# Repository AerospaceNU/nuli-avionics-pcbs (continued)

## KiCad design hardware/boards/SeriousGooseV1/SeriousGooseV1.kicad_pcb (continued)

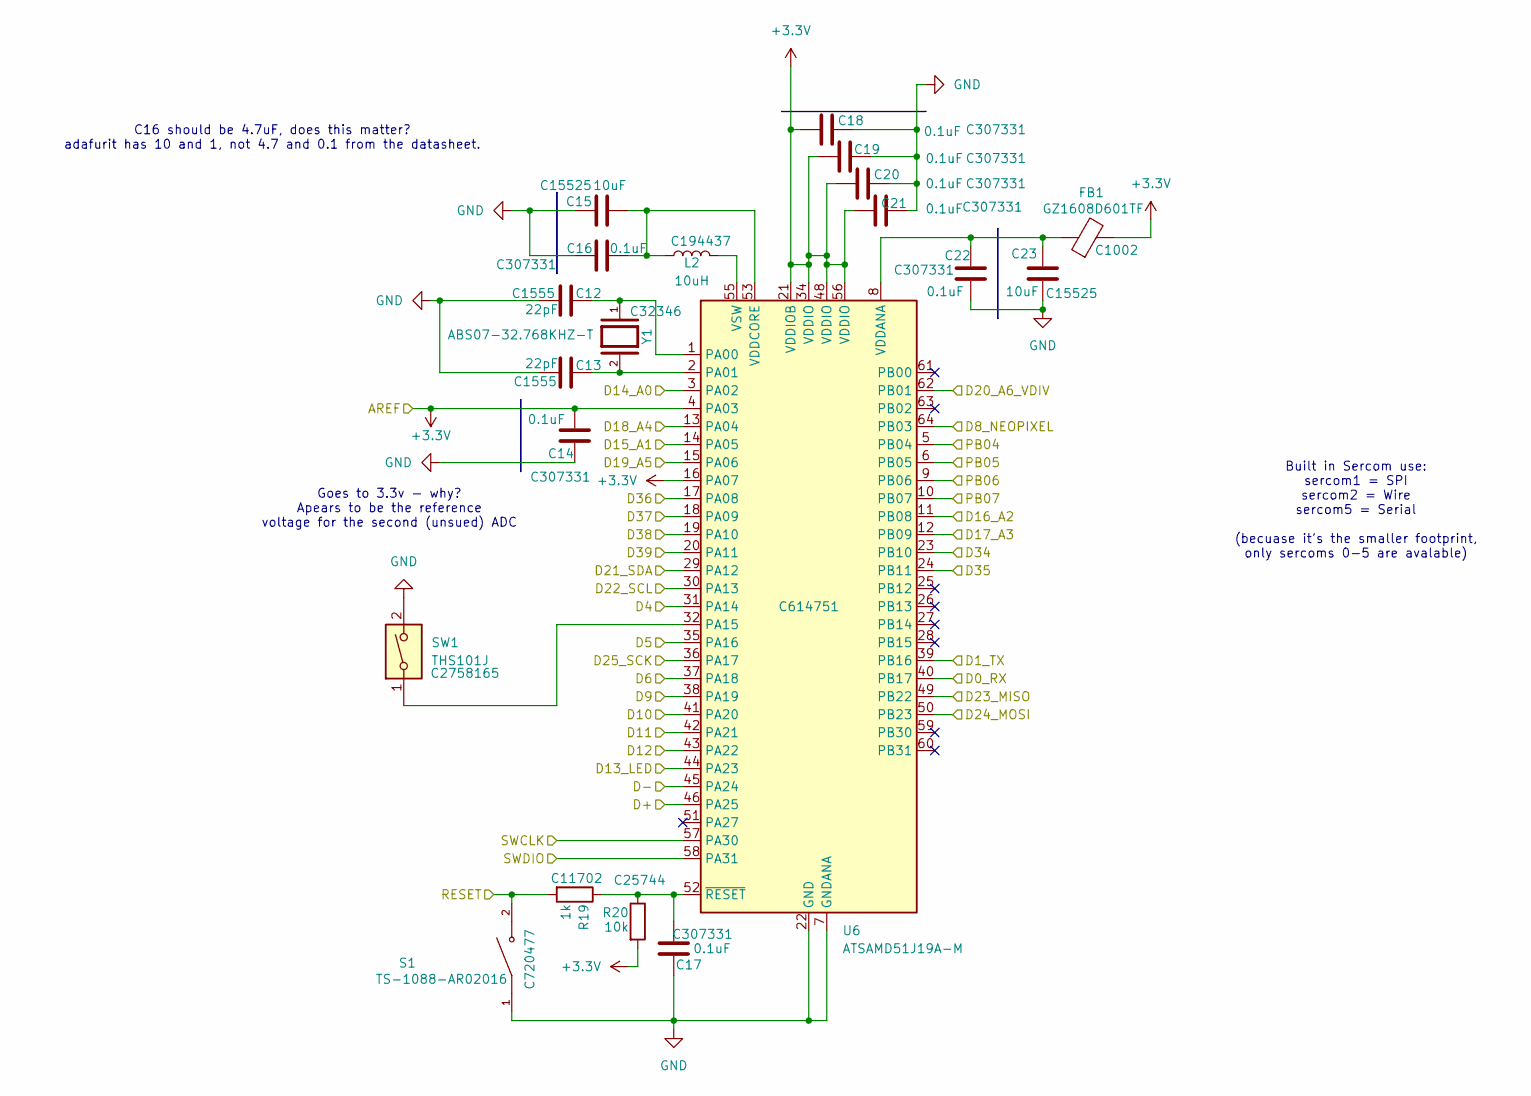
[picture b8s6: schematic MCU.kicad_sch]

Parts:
C12, C13: 22pF; C_0402_1005Metric; LCSC C1555
C14, C16, C17, C18, C19, C20, C21, C22: 0.1uF; C_0402_1005Metric; LCSC C307331
C15, C23: 10uF; C_0402_1005Metric; LCSC C15525
FB1: GZ1608D601TF; L_0603_1608Metric; LCSC C1002
L2: 10uH; L_0603_1608Metric; LCSC C194437
R19: 1k; R_0402_1005Metric; LCSC C11702
R20: 10k; R_0402_1005Metric; LCSC C25744
S1: TS-1088-AR02016; SW_TS-1088-AR02016; PARTREV N/A; LCSC C720477
SW1: THS101J; CHS-01TA; LCSC C2758165
U6: ATSAMD51J19A-M; QFN-64-1EP_9x9mm_P0.5mm_EP4.7x4.7mm; LCSC C614751
Y1: ABS07-32.768KHZ-T; XTAL_ABS07-32.768KHZ-T; PARTREV 08.19.15; LCSC C32346

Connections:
+3.3V: C14.2, C18.1, C19.1, C20.1, C21.1, FB1.2, R20.2, U6.4 (PA03), U6.16 (PA07), U6.21 (VDDIOB), U6.34 (VDDIO), U6.48 (VDDIO), U6.56 (VDDIO); also elsewhere on the board
/Connectors/AUX_1: U6.14 (PA05); also elsewhere on the board
/Connectors/AUX_2: U6.13 (PA04); also elsewhere on the board
/Connectors/AUX_3: U6.3 (PA02); also elsewhere on the board
/Connectors/D+: U6.46 (PA25); also elsewhere on the board
/Connectors/D-: U6.45 (PA24); also elsewhere on the board
/Connectors/RESET: R19.2, S1.2; also elsewhere on the board
/Connectors/SWCLK: U6.57 (PA30); also elsewhere on the board
/Connectors/SWDIO: U6.58 (PA31); also elsewhere on the board
/MCU/D0_RX: U6.40 (PB17); also elsewhere on the board
/MCU/D1_TX: U6.39 (PB16); also elsewhere on the board
/MCU/D4: U6.31 (PA14); also elsewhere on the board
/MCU/D5: U6.35 (PA16); also elsewhere on the board
/MCU/D6: U6.37 (PA18); also elsewhere on the board
/MCU/D8_NEOPIXEL: U6.64 (PB03)
/MCU/D9: U6.38 (PA19); also elsewhere on the board
/MCU/D10: U6.41 (PA20); also elsewhere on the board
/MCU/D11: U6.42 (PA21); also elsewhere on the board
/MCU/D12: U6.43 (PA22); also elsewhere on the board
/MCU/D13_LED: U6.44 (PA23)
/MCU/D16_A2: U6.11 (PB08); also elsewhere on the board
/MCU/D17_A3: U6.12 (PB09); also elsewhere on the board
/MCU/D19_A5: U6.15 (PA06); also elsewhere on the board
/MCU/D20_A6_VDIV: U6.62 (PB01); also elsewhere on the board
/MCU/D21_SDA: U6.29 (PA12); also elsewhere on the board
/MCU/D22_SCL: U6.30 (PA13); also elsewhere on the board
/MCU/D23_MISO: U6.49 (PB22); also elsewhere on the board
/MCU/D24_MOSI: U6.50 (PB23); also elsewhere on the board
/MCU/D25_SCK: U6.36 (PA17); also elsewhere on the board
/MCU/D34: U6.23 (PB10); also elsewhere on the board
/MCU/D35: U6.24 (PB11); also elsewhere on the board
/MCU/D36: U6.17 (PA08); also elsewhere on the board
/MCU/D37: U6.18 (PA09); also elsewhere on the board
/MCU/D38: U6.19 (PA10); also elsewhere on the board
/MCU/D39: U6.20 (PA11); also elsewhere on the board
/MCU/PB04: U6.5 (PB04); also elsewhere on the board
/MCU/PB05: U6.6 (PB05); also elsewhere on the board
/MCU/PB06: U6.9 (PB06); also elsewhere on the board
/MCU/PB07: U6.10 (PB07); also elsewhere on the board
GND: C12.2, C13.2, C14.1, C15.1, C16.2, C17.1, C18.2, C19.2, C20.2, C21.2, C22.2, C23.2, S1.1, SW1.2, U6.7 (GNDANA), U6.22 (GND), U6.33 (GND), U6.47 (GND), U6.54 (GND), U6.65 (GND); also elsewhere on the board
unnamed: C12.1, U6.1 (PA00), Y1.1
unnamed: C13.1, U6.2 (PA01), Y1.2
unnamed: SW1.1, U6.32 (PA15)
unnamed: C22.1, C23.1, FB1.1, U6.8 (VDDANA)
unnamed: C15.2, C16.1, L2.1, U6.53 (VDDCORE)
unnamed: L2.2, U6.55 (VSW)
unnamed: C17.2, R19.1, R20.1, U6.52 (~RESET)

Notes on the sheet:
Goes to 3.3v - why? Apears to be the reference voltage for the second (unsued) ADC
C16 should be 4.7uF, does this matter? adafurit has 10 and 1, not 4.7 and 0.1 from the datasheet.
Built in Sercom use: sercom1 = SPI sercom2 = Wire sercom5 = Serial (becuase it's the smaller footprint, only sercoms 0-5 are avalable)

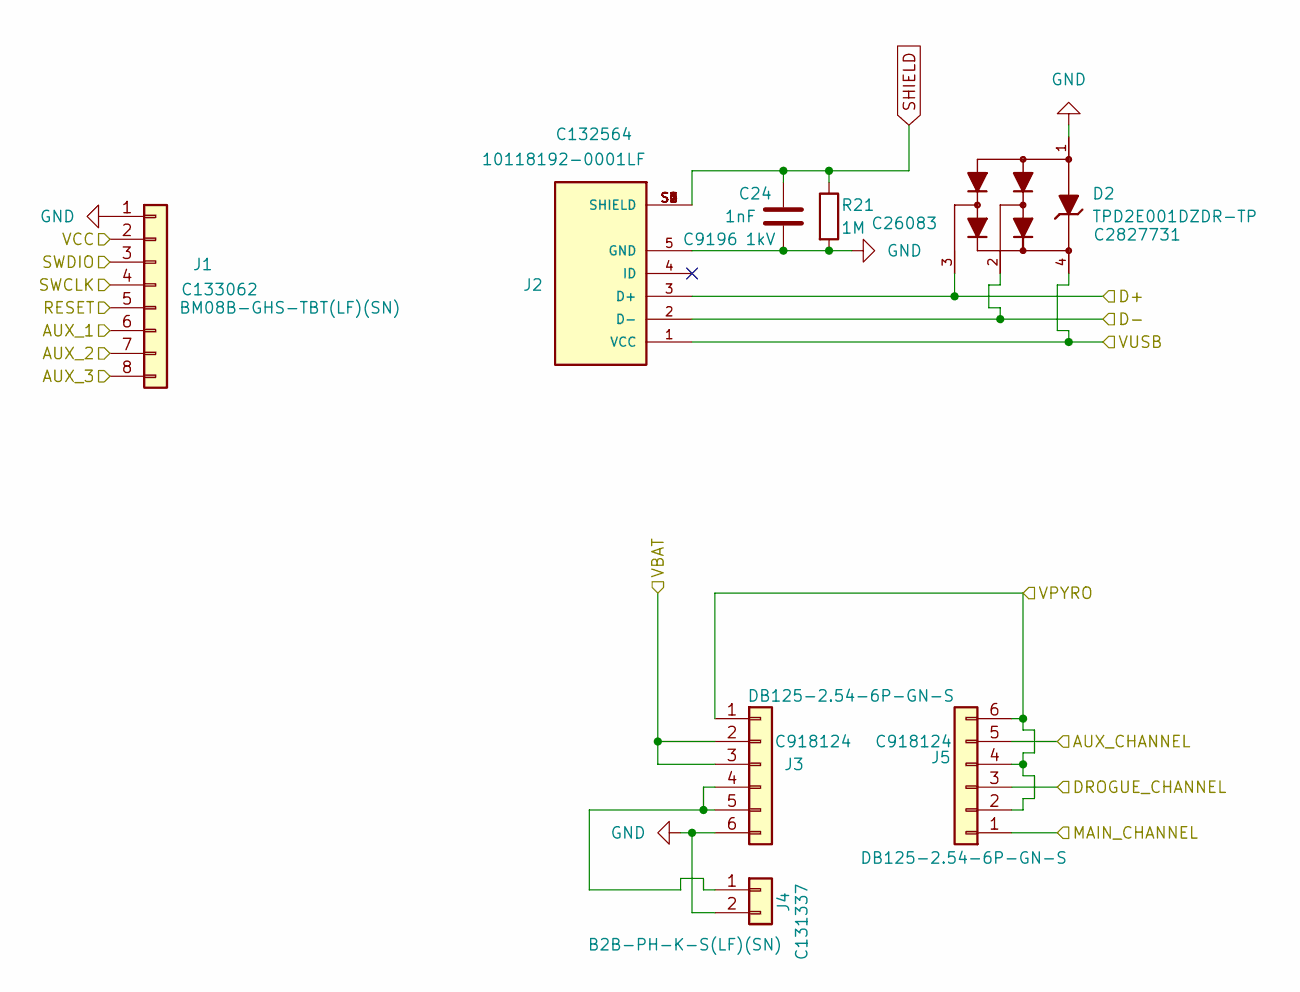
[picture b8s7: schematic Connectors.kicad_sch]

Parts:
C24: 1nF; C_1206_3216Metric; Voltage 1kV; LCSC C9196
D2: TPD2E001DZDR-TP; SOT143B; LCSC C2827731
J1: BM08B-GHS-TBT(LF)(SN); JST_GH_BM08B-GHS-TBT_1x08-1MP_P1.25mm_Vertical; LCSC C133062
J2: 10118192-0001LF; HIROSE_ZX62-AB-5PA_31_; PARTREV Jan 1, 2022; LCSC C132564
J3, J5: DB125-2.54-6P-GN-S; TE_282834-6; LCSC C918124
J4: B2B-PH-K-S(LF)(SN); JST_PH_B2B-PH-K_1x02_P2.00mm_Vertical; LCSC C131337
R21: 1M; R_0402_1005Metric; LCSC C26083

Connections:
+3.3V: J1.2; also elsewhere on the board
+BATT: J3.2, J3.3; also elsewhere on the board
/Connectors/AUX_1: J1.6; also elsewhere on the board
/Connectors/AUX_2: J1.7; also elsewhere on the board
/Connectors/AUX_3: J1.8; also elsewhere on the board
/Connectors/AUX_CHANNEL: J5.5; also elsewhere on the board
/Connectors/D+: D2.3, J2.3 (D+); also elsewhere on the board
/Connectors/D-: D2.2, J2.2 (D-); also elsewhere on the board
/Connectors/DROGUE_CHANNEL: J5.3; also elsewhere on the board
/Connectors/MAIN_CHANNEL: J5.1; also elsewhere on the board
/Connectors/RESET: J1.5; also elsewhere on the board
/Connectors/SWCLK: J1.4; also elsewhere on the board
/Connectors/SWDIO: J1.3; also elsewhere on the board
/Connectors/VPYRO: J3.1, J5.2, J5.4, J5.6; also elsewhere on the board
/Connectors/VUSB: D2.4, J2.1 (VCC); also elsewhere on the board
GND: C24.2, D2.1, J1.1, J2.5 (GND), J3.6, J4.2, R21.2; also elsewhere on the board
unnamed: J3.4, J3.5, J4.1
SHIELD: C24.1, J2.S1 (SHIELD), J2.S2 (SHIELD), J2.S3 (SHIELD), J2.S4 (SHIELD), J2.S5 (SHIELD), J2.S6 (SHIELD), R21.1

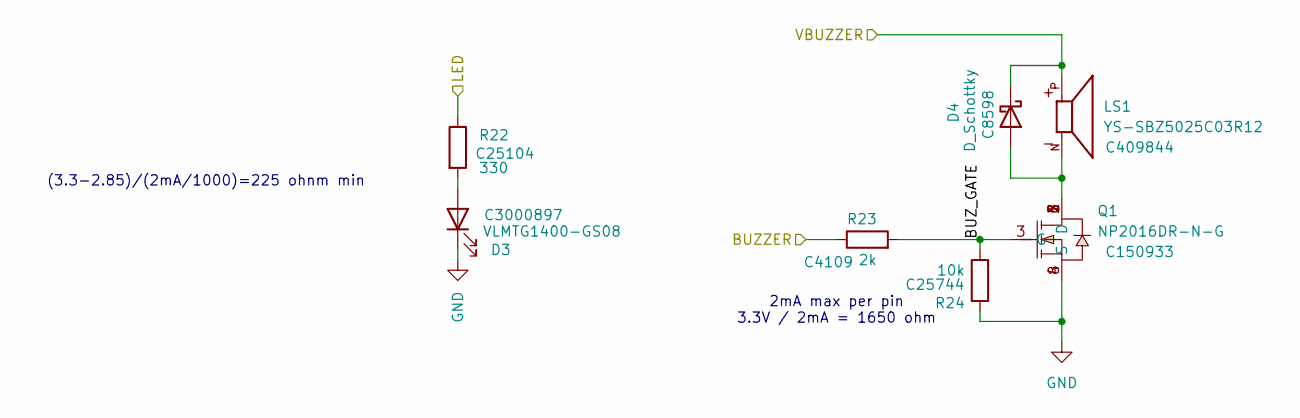
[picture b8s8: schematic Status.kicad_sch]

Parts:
D3: VLMTG1400-GS08; LED_0603_1608Metric; LCSC C3000897
D4: D_Schottky; D_SOD-123; LCSC C8598
LS1: YS-SBZ5025C03R12; XDCR_CMT-0525-75-SMT-TR; PARTREV 1.0; LCSC C409844
Q1: NP2016DR-N-G; U-DFN2020-6; LCSC C150933
R22: 330; R_0402_1005Metric; LCSC C25104
R23: 2k; R_0402_1005Metric; LCSC C4109
R24: 10k; R_0402_1005Metric; LCSC C25744

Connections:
+3.3V: D4.1 (K), LS1.P; also elsewhere on the board
/MCU/D4: R23.1; also elsewhere on the board
/MCU/D5: R22.1; also elsewhere on the board
/Status/BUZ_GATE: Q1.3 (G), R23.2, R24.2
GND: D3.1 (K), Q1.4 (S), Q1.8 (S), R24.1; also elsewhere on the board
unnamed: D3.2 (A), R22.2
unnamed: D4.2 (A), LS1.N, Q1.1 (D), Q1.2 (D), Q1.5 (D), Q1.6 (D), Q1.7 (D)

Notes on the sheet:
2mA max per pin 3.3V / 2mA = 1650 ohm
(3.3-2.85)/(2mA/1000)=225 ohnm min

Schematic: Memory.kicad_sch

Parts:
C6: 10uF; C_0402_1005Metric; LCSC C15525
C7: 2.2uF; C_0402_1005Metric; LCSC C12530
C8: 0.1uF; C_0402_1005Metric; LCSC C307331
IC1: W25Q256JVFIQ; SOIC127P1030X265-16N; Mouser Part Number 727-S25FL512SAGMFV00
R13, R14, R25, R34, R35: 10k; R_0402_1005Metric; LCSC C25744
R15, R16: 100k; R_0402_1005Metric; LCSC C25741
U3: MB85RS64V; SOIC127P600X155-8_R159_68_374R15; LCSC C126731

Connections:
+3.3V: C6.2, C7.1, C8.1, IC1.2 (VCC), R13.1, R14.1, R15.2, R16.1, R25.2, R34.2, R35.2, U3.8 (VCC); also elsewhere on the board
/MCU/D12: IC1.7 (CS#), R35.1; also elsewhere on the board
/MCU/D23_MISO: IC1.8 (SO/IO1), U3.2 (MISO); also elsewhere on the board
/MCU/D24_MOSI: IC1.15 (SI/IO0), U3.5 (MOSI); also elsewhere on the board
/MCU/D25_SCK: IC1.16 (SCK), U3.6 (SCK); also elsewhere on the board
/MCU/D34: R34.1, U3.1 (~CS); also elsewhere on the board
/MCU/PB06: R14.2, U3.7 (~HOLD); also elsewhere on the board
/MCU/PB07: IC1.1 (HOLD#/IO3), R25.1; also elsewhere on the board
GND: C6.1, C7.2, C8.2, IC1.10 (VSS), U3.4 (GND); also elsewhere on the board
unnamed: IC1.3 (RESET#/RFU), R15.1
unnamed: IC1.9 (WP#/IO2), R16.2
unnamed: R13.2, U3.3 (~WP)

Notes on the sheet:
ALT:MX25L25645GMI-08G
get the 512 one?
Internal pullup on WP

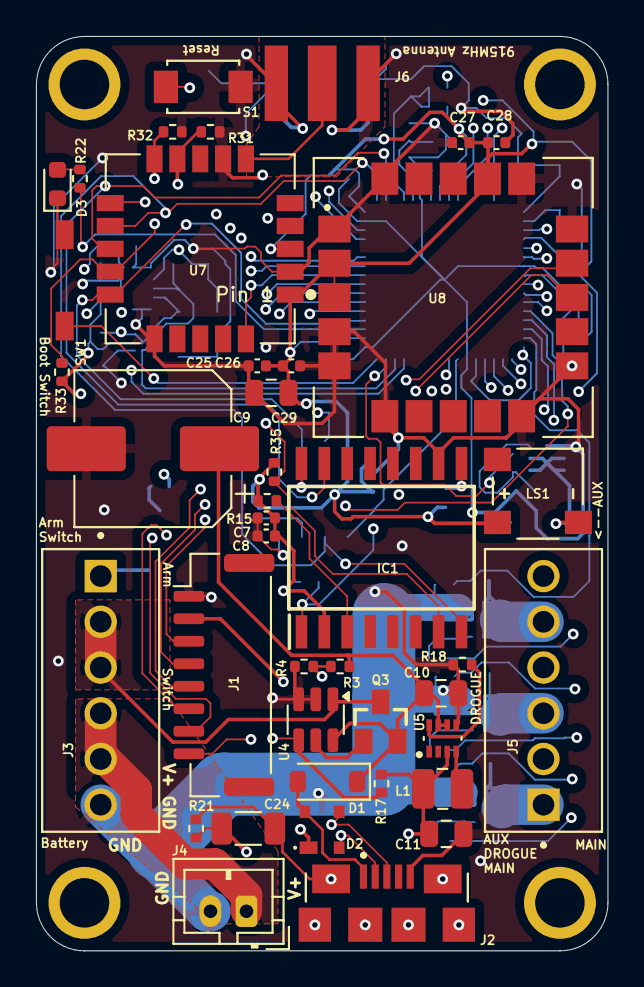
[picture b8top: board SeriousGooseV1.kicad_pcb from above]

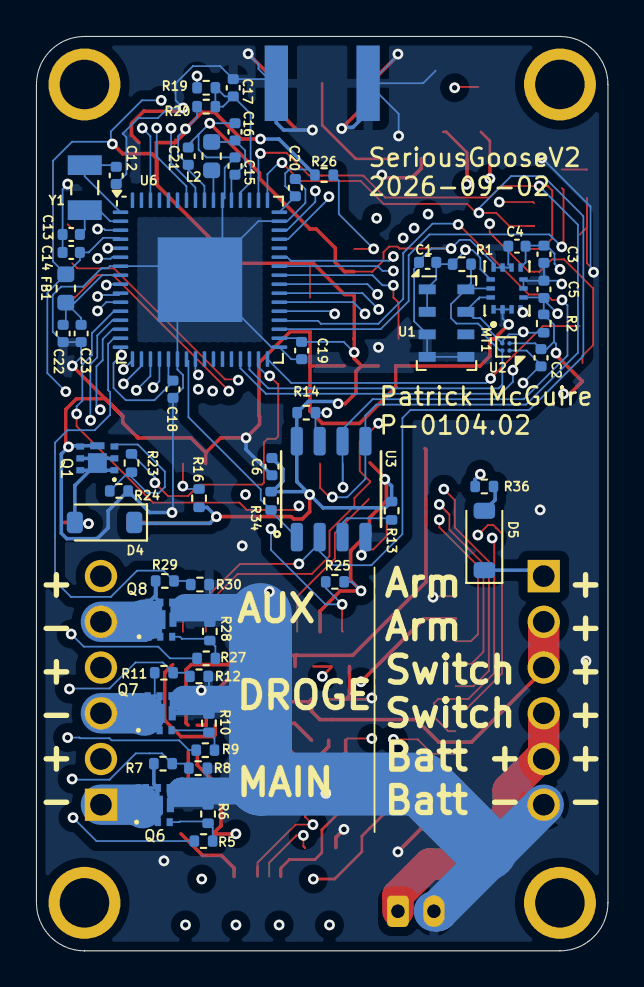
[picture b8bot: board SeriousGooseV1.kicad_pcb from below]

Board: 4 copper layers, 31.8 x 50.8 mm, 102 parts (57 on the bottom side), 68 nets.

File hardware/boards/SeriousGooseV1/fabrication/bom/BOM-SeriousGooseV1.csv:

Comment,Designator,Footprint,LCSC,Quantity
0.1uF,"C1,C14,C16,C17,C18,C19,C20,C21,C22,C26,C28,C3,C8",C_0402_1005Metric,C307331,13
100k,"R15,R16,R36",R_0402_1005Metric,C25741,3
10118192-0001LF,J2,HIROSE_ZX62-AB-5PA_31_,C132564,1
10k,"R10,R12,R13,R14,R20,R24,R25,R26,R28,R30,R31,R32,R33,R34,R35,R4,R6,R8",R_0402_1005Metric,C25744,18
10nF,C5,C_0402_1005Metric,C15195,1
10uF,"C15,C23,C25,C27,C6",C_0402_1005Metric,C15525,5
10uH,L2,L_0603_1608Metric,C194437,1
1M,"R17,R21",R_0402_1005Metric,C26083,2
1k,R19,R_0402_1005Metric,C11702,1
1nF,C24,C_1206_3216Metric,C9196,1
2.2uF,"C2,C4,C7",C_0402_1005Metric,C12530,3
220uF,C9,CP_Elec_8x10.5,C970697,1
22pF,"C12,C13",C_0402_1005Metric,C1555,2
22uF,"C10,C11,C29",C_0805_2012Metric,C45783,3
2k,"R23,R27,R5,R9",R_0402_1005Metric,C4109,4
3.3k,"R1,R2",R_0402_1005Metric,C25890,2
330,R22,R_0402_1005Metric,C25104,1
34k,R18,R_0402_1005Metric,C48939,1
47k,"R11,R29,R3,R7",R_0402_1005Metric,C25792,4
ABS07-32.768KHZ-T,Y1,XTAL_ABS07-32.768KHZ-T,C32346,1
AO3401A,Q3,SSOT-3,C15127,1
ATSAMD51J19A-M,U6,QFN-64-1EP_9x9mm_P0.5mm_EP4.7x4.7mm,C614751,1
B2B-PH-K-S(LF)(SN),J4,JST_PH_B2B-PH-K_1x02_P2.00mm_Vertical,C131337,1
BM08B-GHS-TBT(LF)(SN),J1,JST_GH_BM08B-GHS-TBT_1x08-1MP_P1.25mm_Vertical,C133062,1
BWSMA-KE-P001,J6,BATWIRELESS_BWSMA-KE-P001,C496550,1
DB125-2.54-6P-GN-S,"J3,J5",TE_282834-6,C918124,2
DFE252012PD-2R2M=P2,L1,L_1008_2520Metric,C237482,1
D_Schottky,"D1,D4,D5",D_SOD-123,C8598,3
E22-900MM22S,U7,E22-900MM22S,C5333985,1
GZ1608D601TF,FB1,L_0603_1608Metric,C1002,1
ICM-42605,MT1,XDCR_ICM-42605,C2655099,1
LTC4412xS6,U4,TSOT-23-6,C514442,1
MB85RS64V,U3,SOIC127P600X155-8_R159_68_374R15,C126731,1
MMC5603NJ,U2,WLP-4_0.86x0.86mm_P0.4mm,C404328,1
MS5607-02BA,U1,LGA-8_3x5mm_P1.25mm,C97627,1
NP2016DR-N-G,"Q1,Q6,Q7,Q8",U-DFN2020-6,C150933,4
SAM-M10Q-00B,U8,XCVR_SAM-M10Q-00B,C5447387,1
THS101J,SW1,CHS-01TA,C2758165,1
TPD2E001DZDR-TP,D2,SOT143B,C2827731,1
TPS629210DRLR,U5,SOT50P160X60-8N,C5219301,1
TS-1088-AR02016,S1,SW_TS-1088-AR02016,C720477,1
VLMTG1400-GS08,D3,LED_0603_1608Metric,C3000897,1
W25Q256JVFIQ,IC1,SOIC127P1030X265-16N,C779876,1
YS-SBZ5025C03R12,LS1,XDCR_CMT-0525-75-SMT-TR,C409844,1
